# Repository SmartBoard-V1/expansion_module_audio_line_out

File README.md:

# Expansion Module: Audio Line Out with CS4344

## Overview
This repository houses the design and development of the CS4344 Audio Line Out Expansion Module, specifically engineered for integration with the SmartBoard platform. The CS4344 module, featuring a compact and high-performance digital-to-analog converter (DAC), provides a superior stereo audio output capability. Designed to fit seamlessly into a single expansion slot on the SmartBoard, this module utilizes a standard I2S interface for integration, making it an exemplary choice for projects requiring high-fidelity audio playback and audio effects and filters development.

## Key Features of CS4344
- **24-bit Resolution**: Delivers high-fidelity audio with a 24-bit data converter, ensuring detailed and rich sound reproduction.
- **Stereo Audio Output**: Provides high-quality stereo sound output, significantly enhancing the audio playback experience.
- **Integrated CS4344 DAC**: Incorporates the CS4344 DAC for advanced audio performance, capable of handling sample rates up to 192 kHz, allowing for studio-quality sound.
- **SmartBoard Compatibility**: Specifically designed for the SmartBoard platform, this module fits into a single expansion slot, offering a compact and efficient audio output solution.
- **Standard I2S Interface**: Features a widely supported I2S interface for straightforward integration, facilitating ease of use with a broad array of microcontrollers and DSPs.
- **Dynamic Range**: Boasts an impressive dynamic range, catering to a wide spectrum of audio applications, from basic audio playback to complex audio processing for development and educational purposes.

## Design Documentation

Below are the key design documents for the CS4344 Audio Line Out Expansion Module, including schematic diagrams and board designs. These documents offer detailed insights into the module's architecture and layout, facilitating understanding and modifications.

### Schematic Diagram

*This is the schematic diagram of the CS4344 Audio Line Out Expansion Module, showing the connection and configuration of the CS4344 DAC and other components.*

### Board Design - 2D

*The 2D board design displays the physical layout of the module's components on the PCB, aiding in assembly and troubleshooting.*

### Board Design - 3D Visualization

*This 3D visualization provides a comprehensive view of the module, offering a clearer understanding of its physical characteristics and design considerations.*

### CS4344 DAC Documentation
For more detailed information about the CS4344 DAC, refer to the datasheet available [here](media/CS4344_45_48_F2-1141644.pdf).

## Contributions and Feedback
We welcome contributions to this project. If you have suggestions for improvement or have developed additional features, please fork the repository, make your changes, and submit a pull request. For any questions or issues, please open an issue in the GitHub repository.

## License
This audio output project is licensed under the MIT License with the following terms:

- **Permission to Use**: You are free to use, modify, and distribute this audio output design in both private and commercial settings.
- **Attribution Requirement**: While not required, attribution to the original author, Adam Łuczak, is appreciated. This can be done through a citation or a link back to this repository.
- **No Warranty**: This design is provided "as is", without warranty of any kind. Use it at your own risk.
- **Liability**: The author is not liable for any damages or losses that may arise from the use of this design.

For the full terms and conditions, please refer to the MIT License documentation.

## Contact
Should you have any inquiries or suggestions regarding this audio output project, please don't hesitate to contact Adam Łuczak at adam.luczak@outlook.com.

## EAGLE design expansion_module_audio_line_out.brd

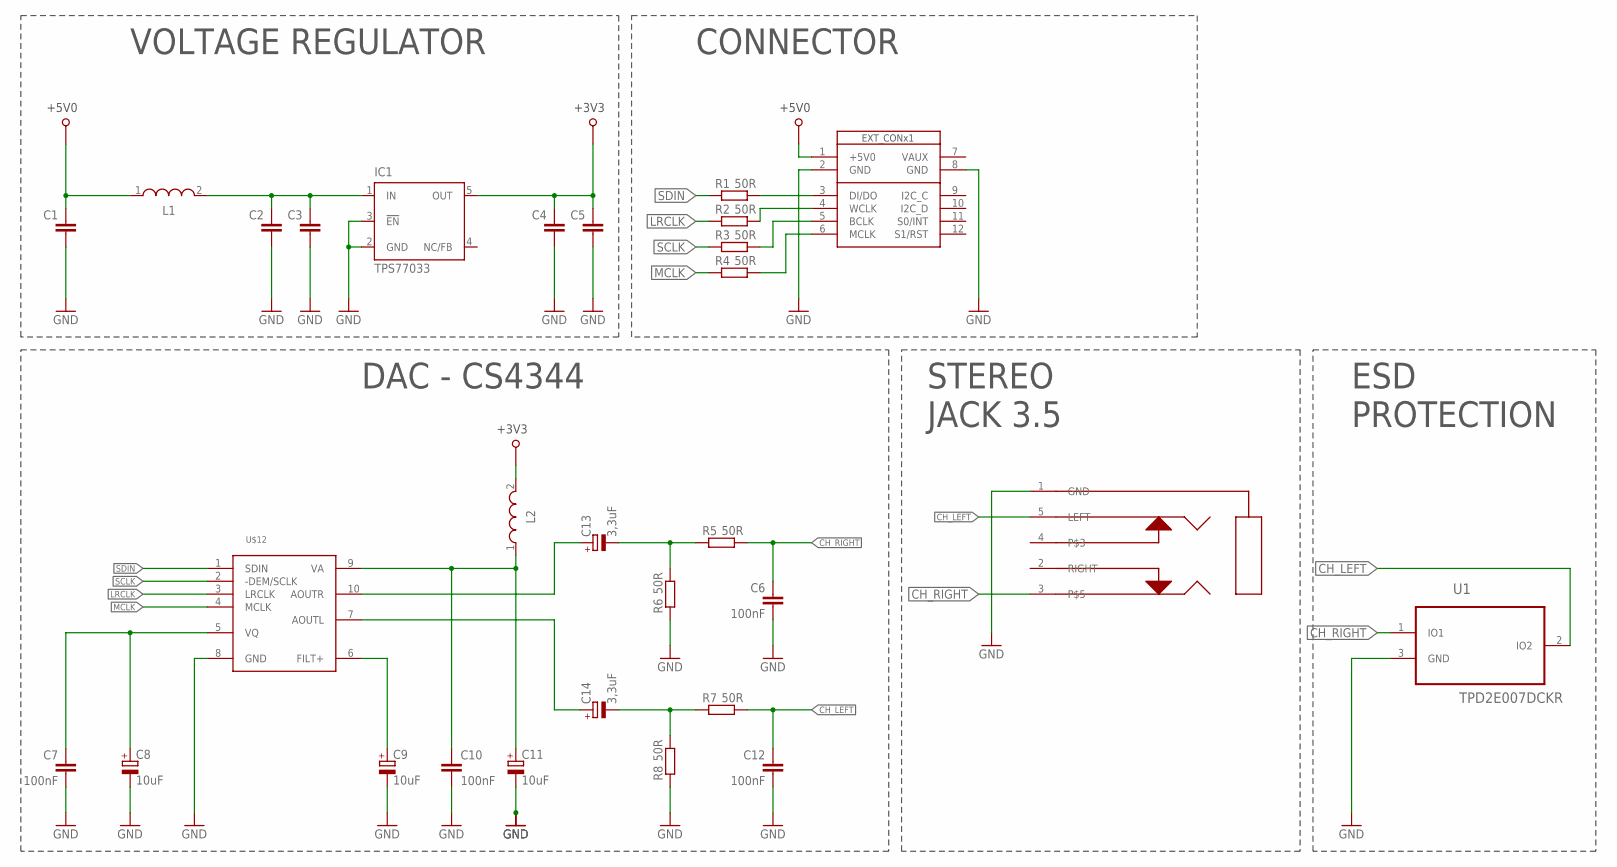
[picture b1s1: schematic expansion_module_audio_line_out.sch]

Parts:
C1, C2, C3, C4, C5: C-EUC0805; C0805
C6, C7, C10, C12: 100nF; C0805
C8, C9, C11: 10uF; SMC_A
C13, C14: 3,3uF; SMC_A
IC1: TPS77033; SOT23-DBV
L1, L2: WE-LQ_1210; WE-LQ_M
R1, R2, R3, R4, R5, R6, R7, R8: 50R; R0805
U1: TPD2E007DCKR; SOT65P210X110-3N
U$1: SB_EXT_CON_X1_I2S; SB_EXT_CON_X1_FULL
U$12: CS4344; MSOP10
U$27: JACK_STEREO_5_PIN

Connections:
+3V3: C4.2, C5.2, IC1.5 (OUT), L2.2
+5V0: C1.2, L1.1, U$1.1 (+5V0)
CH_LEFT: C12.2, R7.2, U1.2 (IO2), U$27.5 (LEFT)
CH_RIGHT: C6.2, R5.2, U1.1 (IO1), U$27.3
GND: C1.1, C2.1, C3.1, C4.1, C5.1, C6.1, C7.1, C8.-, C9.-, C10.1, C11.-, C12.1, IC1.2 (GND), IC1.3 (!EN), R6.1, R8.1, U1.3 (GND), U$1.2 (GND), U$1.8 (GND), U$12.8 (GND), U$27.1 (GND)
LRCLK: R2.1, U$12.3 (LRCLK)
MCLK: R4.1, U$12.4 (MCLK)
unnamed: R1.2, U$1.3 (DI/DO)
unnamed: R2.2, U$1.4 (WCLK)
unnamed: R3.2, U$1.5 (BCLK)
unnamed: R4.2, U$1.6 (MCLK)
unnamed: C9.+, U$12.6 (FILT+)
unnamed: C7.2, C8.+, U$12.5 (VQ)
unnamed: C10.2, C11.+, L2.1, U$12.9 (VA)
unnamed: C2.2, C3.2, IC1.1 (IN), L1.2
unnamed: C14.-, R7.1, R8.2
unnamed: C13.+, U$12.10 (AOUTR)
unnamed: C13.-, R5.1, R6.2
unnamed: C14.+, U$12.7 (AOUTL)
SCLK: R3.1, U$12.2 (-DEM/SCLK)
SDIN: R1.1, U$12.1 (SDIN)

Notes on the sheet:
CONNECTOR
VOLTAGE REGULATOR
DAC - CS4344
STEREO JACK 3.5
ESD PROTECTION

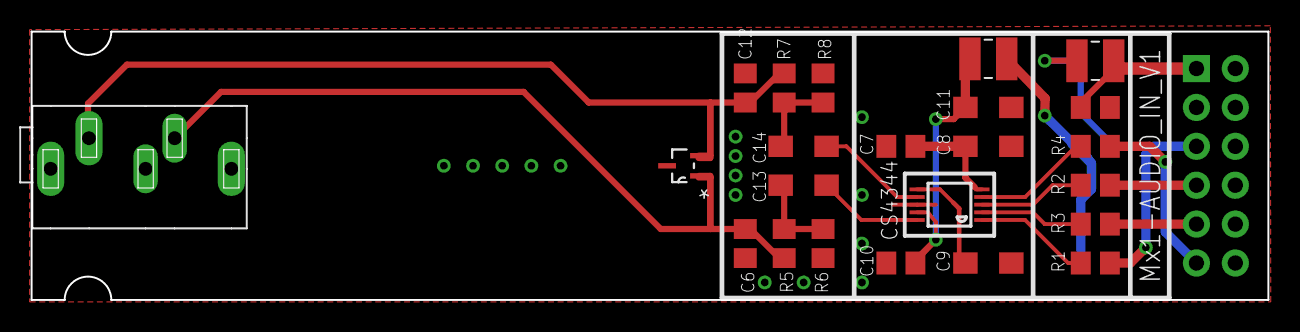
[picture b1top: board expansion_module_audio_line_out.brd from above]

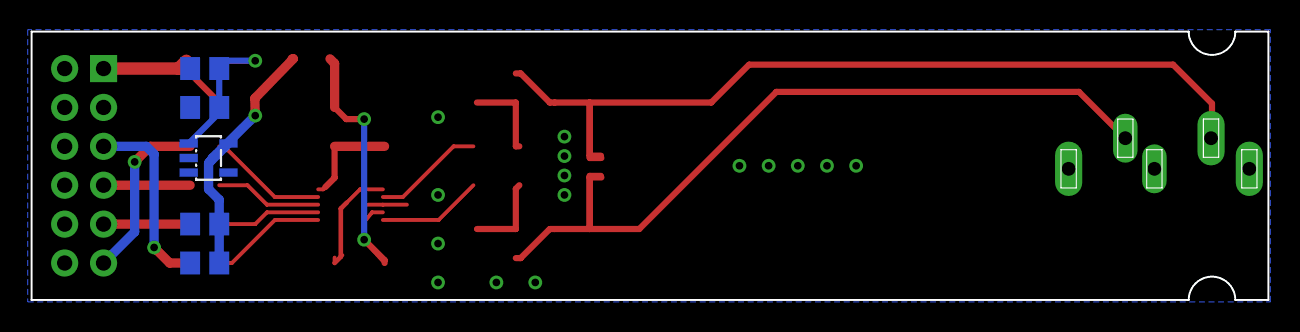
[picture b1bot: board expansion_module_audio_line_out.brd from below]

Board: 2 copper layers, 80.8 x 17.5 mm, 29 parts (5 on the bottom side), 21 nets.

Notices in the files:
README.md:
License: MIT
parts and their libraries:
EagleLibrary_Wuerth_Elektronik_eiSos_rev: Copyright: Würth Elektronik
cirrus-3: Copyright (C) 2005 by Bob Starr, rtzaudio@mindspring.com
